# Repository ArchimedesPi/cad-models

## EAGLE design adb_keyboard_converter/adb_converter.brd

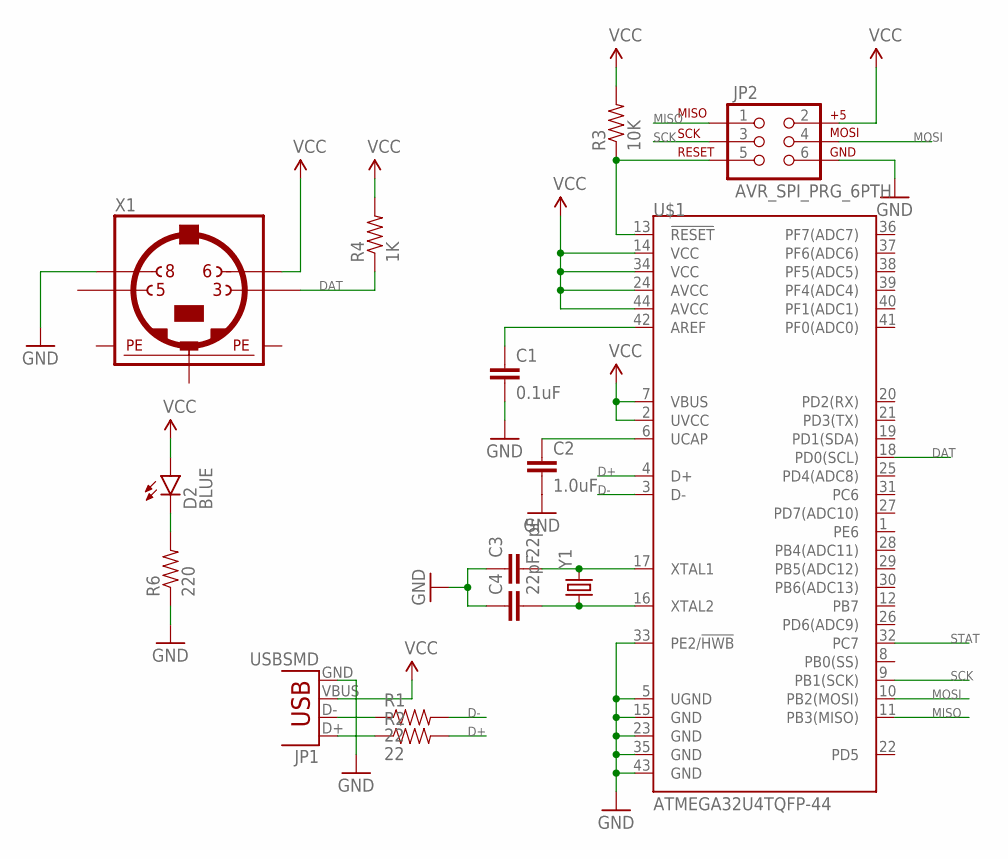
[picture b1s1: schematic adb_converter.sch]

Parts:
C1: 0.1uF; 0603-CAP
C2: 1.0uF; 0603-CAP
C3, C4: 22pF; 0603-CAP
D2: BLUE; LED-0603
JP1: USBSMD; USB-MINIB
JP2: AVR_SPI_PRG_6PTH; 2X3
R1, R2: 22; 0603-RES
R3: 10K; 0603-RES
R4: 1K; 0603-RES
R6: 220; 0603-RES
U$1: ATMEGA32U4TQFP-44; TQFP44
X1: MINI_DIN_4; M_DIN4
Y1: CRYSTALHC49US; HC49US

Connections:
D+: R2.2, U$1.4 (D+)
D-: R1.2, U$1.3 (D-)
DAT: R4.1, U$1.18 (PD0(SCL)), X1.3
GND: C1.2, C2.2, C3.1, C4.1, JP1.GND, JP2.6, R6.1, U$1.5 (UGND), U$1.15 (GND), U$1.23 (GND), U$1.33 (PE2/!HWB), U$1.35 (GND), U$1.43 (GND), X1.8
MISO: JP2.1, U$1.11 (PB3(MISO))
MOSI: JP2.4, U$1.10 (PB2(MOSI))
unnamed: JP1.D-, R1.1
unnamed: JP1.D+, R2.1
unnamed: JP2.5, R3.1, U$1.13 (!RESET)
unnamed: C1.1, U$1.42 (AREF)
unnamed: C2.1, U$1.6 (UCAP)
unnamed: C3.2, U$1.17 (XTAL1), Y1.2
unnamed: C4.2, U$1.16 (XTAL2), Y1.1
unnamed: D2.C, R6.2
PE1: X1.SH1 (PE1)
PE2: X1.SH2 (PE2)
PE3: X1.SH3 (PE3)
SCK: JP2.3, U$1.9 (PB1(SCK))
STAT: U$1.32 (PC7)
VCC: D2.A, JP1.VBUS, JP2.2, R3.2, R4.2, U$1.2 (UVCC), U$1.7 (VBUS), U$1.14 (VCC), U$1.24 (AVCC), U$1.34 (VCC), U$1.44 (AVCC), X1.6

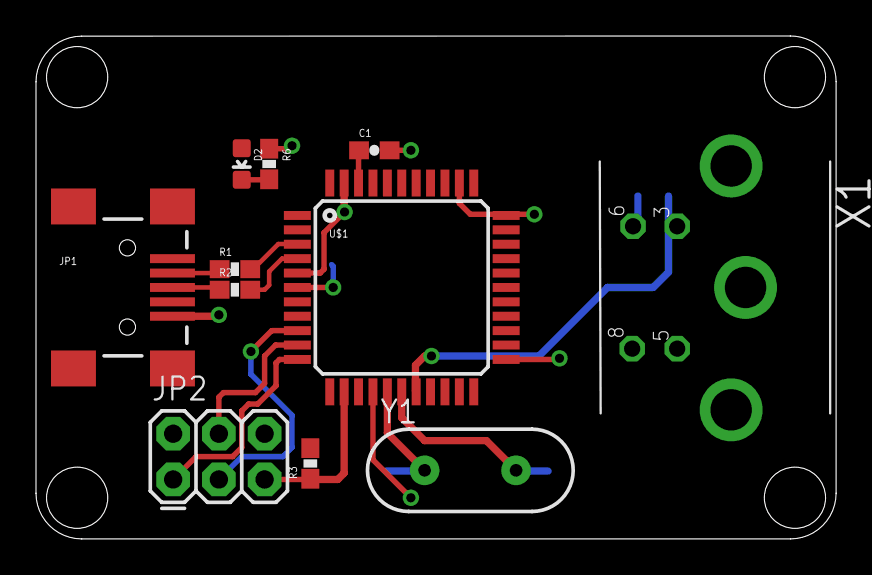
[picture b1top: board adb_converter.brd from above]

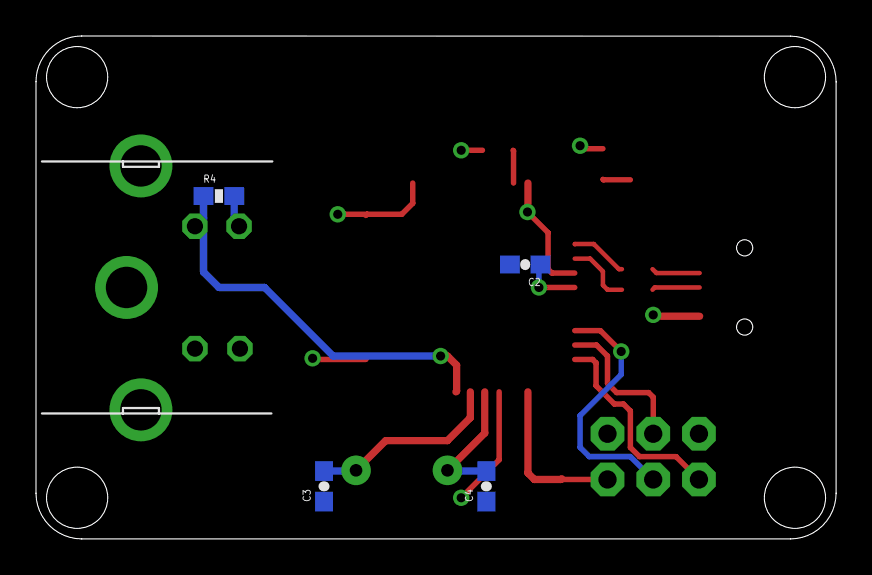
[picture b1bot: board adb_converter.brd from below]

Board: 2 copper layers, 44.5 x 27.9 mm, 15 parts (4 on the bottom side), 16 nets.

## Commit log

2015-05-23 :confetti_ball: Added .gitattributes & .gitignore files
2015-05-23 Add ignore for solidworks temp files
2015-05-23 OpenSCAD up a blender lid top
2015-05-23 Add associated STL
2015-05-23 Simplify rim()
2015-05-23 More accurate baseDiameter
2015-05-23 Larger tabs
2015-05-23 Diameter, not radius
2015-05-23 Generally fix model
2015-05-23 Add an icosahedron stl
2015-05-23 Icosahedron mold
2015-05-23 Export icosahedron_mold as stl
2015-05-24 Add pourDiameter to icosahedron_mold.scad
2015-05-24 Increase pour diameter
2015-05-24 Better printing orientation
2015-05-24 epsilon
2015-05-24 reexport stl
2015-05-24 Ran through netfabb
2015-05-24 Go back to the old orientation
2015-05-24 Update STLs
2015-05-25 A candlestick for 22mm candles
2015-05-25 ignore .gcode files
2015-05-25 Update candlestick
2015-05-27 Update blender top lid
2015-05-27 Move the tabs higher
2015-05-27 Reexport stls from 7c65f44
2015-11-01 Ignore EAGLE temporary files
2015-11-01 add initial design for adb converter
2015-11-01 finish adb converter design

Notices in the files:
parts and their libraries:
SparkFun-Connectors: Licensing: Creative Commons ShareAlike 4.0 International - https://creativecommons.org/licenses/by-sa/4.0
